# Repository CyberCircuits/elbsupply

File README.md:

## ElbSupply - A simple linear bench supply

ElbSupply is a linear bench power supply with an output voltage range of 0-20V and output current range of 0-3A.

Here are the OSHpark renderings of the boards:

For project details visit the [project page on Hackaday.io](https://hackaday.io/project/4407-elbsupply-simple-linear-bench-supply)

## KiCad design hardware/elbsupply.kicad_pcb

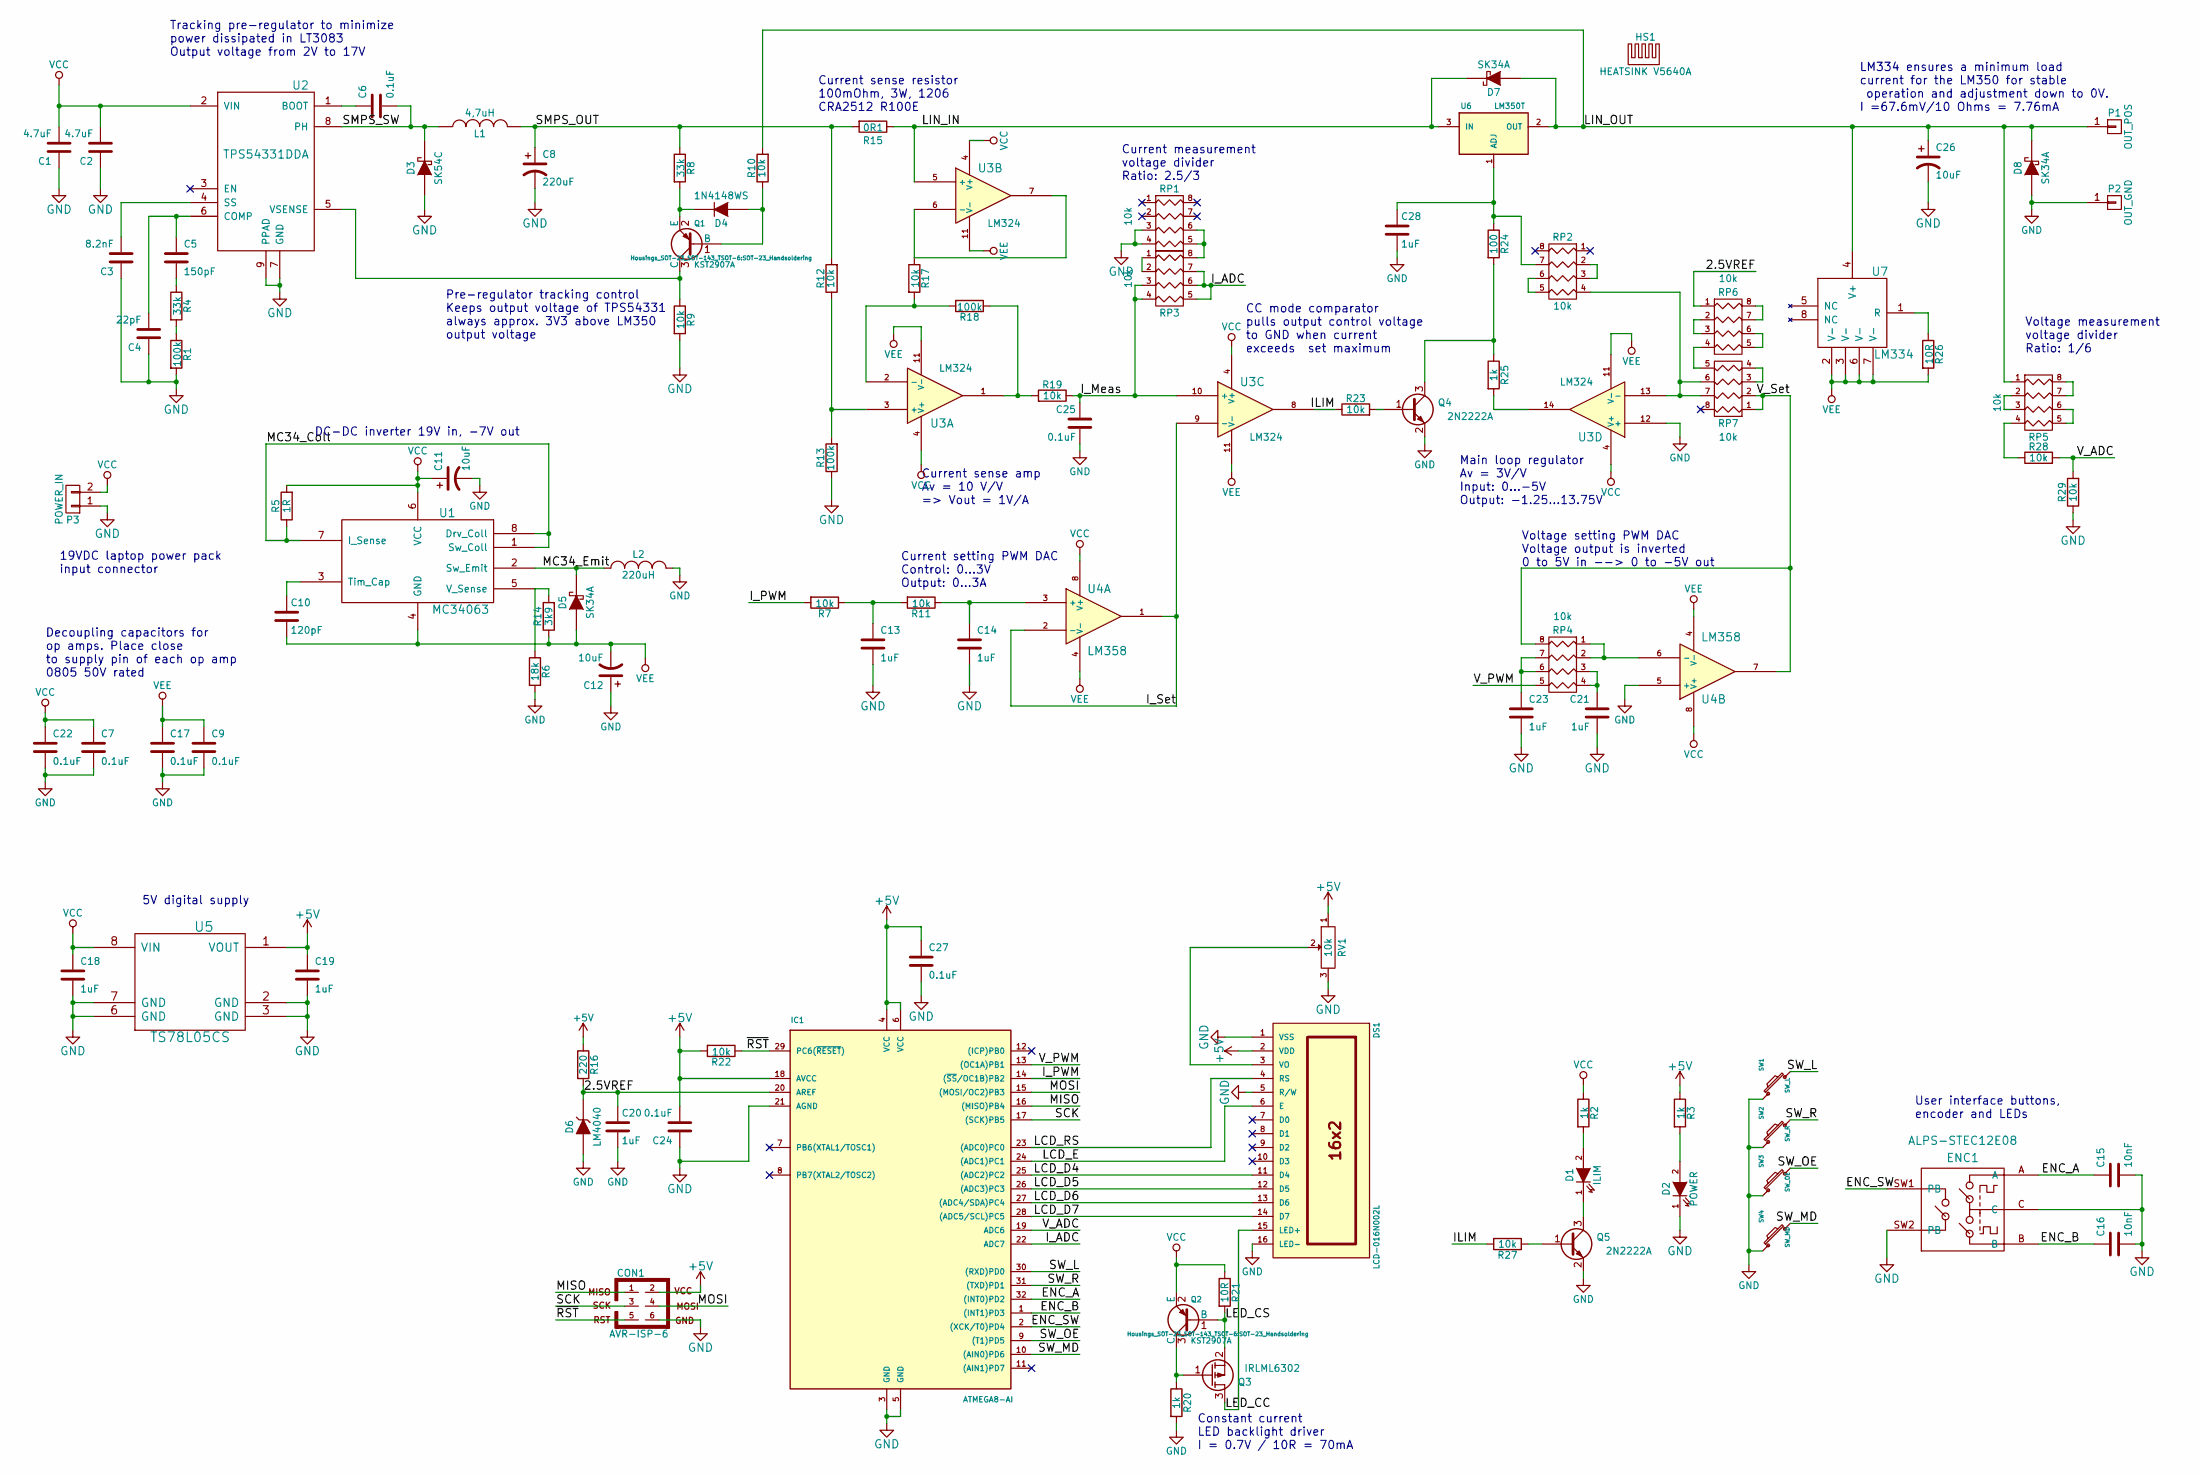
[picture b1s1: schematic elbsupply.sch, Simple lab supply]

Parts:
C1, C2: 4.7uF; C_0805_HandSoldering
C3: 8.2nF; C_0603_HandSoldering
C4: 22pF; C_0603_HandSoldering
C5: 150pF; C_0603_HandSoldering
C6, C7, C9, C17, C22, C24, C25, C27: 0.1uF; C_0805_HandSoldering
C8: 220uF; c_elec_8x10.5
C10: 120pF; C_0603_HandSoldering
C11, C26: 10uF; c_elec_4x4.5
C12: 10uF; C_0805_HandSoldering
C13, C14, C18, C19, C20, C21, C23, C28: 1uF; C_0805_HandSoldering
C15, C16: 10nF; C_0603_HandSoldering
CON1: AVR-ISP-6; Pin_Header_Straight_2x03
D1: ILIM; LED-0805
D2: POWER; LED-0805
D3: SK54C; Diode-SMC_Handsoldering
D4: 1N4148WS; SOD-323
D5, D7, D8: SK34A; DO-214-AC_SMA
D6: LM4040; SOT-23_Handsoldering
DS1: LCD-016N002L; LCD16X2
ENC1: ALPS-STEC12E08
HS1: HEATSINK V5640A; Heatsink-V5640A
IC1: ATMEGA8-AI; TQFP-32_7x7mm_Pitch0.8mm
L1: 4,7uH; 242418FPS-Fastron
L2: 220uH; 242418FPS-Fastron
P1: OUT_POS; SKS-PK10A
P2: OUT_GND; SKS-PK10A
P3: POWER_IN; bornier2
Q1, Q2: KST2907A; SOT-23_Handsoldering
Q3: IRLML6302; SOT-23_Handsoldering
Q4, Q5: 2N2222A; SOT-23_Handsoldering
R1, R13, R18: 100k; R_0603_HandSoldering
R2, R3, R20, R25: 1k; R_0603_HandSoldering
R4, R8: 33k; R_0603_HandSoldering
R5: 1R; R_0805_HandSoldering
R6: 18k; R_0603_HandSoldering
R7, R9, R10, R11, R12, R17, R19, R22, R23, R27, R28, R29: 10k; R_0603_HandSoldering
R14: 3k9; R_0603_HandSoldering
R15: 0R1; CRA2512-Bourns
R16: 220; R_0603_HandSoldering
R21: 10R; R_0603_HandSoldering
R24: 100; R_0603_HandSoldering
R26: 10R; R_0805_HandSoldering
RP1, RP2, RP3, RP4, RP5, RP6, RP7: 10k; YC164-Yageo-Handsoldering
RV1: 10k; BITech-23B
SW1: SW_L; Button-SMT-standard
SW2: SW_R; Button-SMT-standard
SW3: SW_OE; Button-SMT-standard
SW4: SW_MD; Button-SMT-standard
U1: MC34063; SO8
U2: TPS54331DDA; SO8-PowerPAD
U3: LM324; SO14
U4: LM358; SO8
U5: TS78L05CS; SO8
U6: LM350T; TO-220
U7: LM334; SO8

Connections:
+5V: C19.1, C24.2, C27.1, CON1.2, DS1.2 (VDD), IC1.4 (VCC), IC1.6 (VCC), IC1.18 (AVCC), R3.1, R16.1, R22.2, RV1.1, U5.1 (VOUT)
/2.5VREF: C20.1, D6.1 (K), IC1.20 (AREF), R16.2, RP6.1
/ENC_A: C15.1, ENC1.A, IC1.32 ((INT0)PD2)
/ENC_B: C16.1, ENC1.B, IC1.1 ((INT1)PD3)
/ENC_SW: ENC1.SW1 (PB), IC1.2 ((XCK/T0)PD4)
/ILIM: R23.1, R27.2, U3.8
/I_ADC: IC1.22 (ADC7), RP3.5 (R4), RP3.6 (R3), RP3.7 (R2)
/I_Meas: C25.1, R19.1, RP3.3, RP3.4, U3.10 (+)
/I_PWM: IC1.14 ((~SS~/OC1B)PB2), R7.2
/I_Set: U3.9 (-), U4.1, U4.2 (-)
/LCD_D4: DS1.11 (D4), IC1.25 ((ADC2)PC2)
/LCD_D5: DS1.12 (D5), IC1.26 ((ADC3)PC3)
/LCD_D6: DS1.13 (D6), IC1.27 ((ADC4/SDA)PC4)
/LCD_D7: DS1.14 (D7), IC1.28 ((ADC5/SCL)PC5)
/LCD_E: DS1.6 (E), IC1.24 ((ADC1)PC1)
/LCD_RS: DS1.4 (RS), IC1.23 ((ADC0)PC0)
/LED_CC: DS1.15 (LED+), Q3.3 (D)
/LED_CS: Q2.1 (B), Q3.2 (S), R21.2
/LIN_IN: D7.2 (K), R15.1, U3.5 (+), U6.3 (IN)
/LIN_OUT: C26.1, D7.1 (A), D8.2 (K), P1.1, R10.2, RP5.1, U6.2 (OUT), U7.4 (V+)
/MC34_Coll: R5.1, U1.1 (Sw_Coll), U1.7 (I_Sense), U1.8 (Drv_Coll)
/MC34_Emit: D5.2 (K), L2.1, U1.2 (Sw_Emit)
/MISO: CON1.1, IC1.16 ((MISO)PB4)
/MOSI: CON1.4, IC1.15 ((MOSI/OC2)PB3)
/SCK: CON1.3, IC1.17 ((SCK)PB5)
/SMPS_OUT: C8.1, L1.2, R8.1, R12.2, R15.2
/SMPS_SW: C6.2, D3.2 (K), L1.1, U2.8 (PH)
/SW_L: IC1.30 ((RXD)PD0), SW1.2
/SW_MD: IC1.10 ((AIN0)PD6), SW4.2
/SW_OE: IC1.9 ((T1)PD5), SW3.2
/SW_R: IC1.31 ((TXD)PD1), SW2.2
/V_ADC: IC1.19 (ADC6), R28.2, R29.2
/V_PWM: IC1.13 ((OC1A)PB1), RP4.5 (R4)
/V_Set: RP4.8 (R1), RP7.1, RP7.2, U4.7
/~RST~: CON1.5, IC1.29 (PC6(~RESET~)), R22.1
GND: C1.1, C2.1, C3.1, C4.1, C7.2, C8.2, C9.2, C11.2, C12.1, C13.2, C14.2, C15.2, C16.2, C17.2, C18.2, C19.2, C20.2, C21.2, C22.2, C23.2, C24.1, C25.2, C26.2, C27.2, C28.2, CON1.6, D2.1 (K), D3.1 (A), D6.2 (A), D8.1 (A), DS1.1 (VSS), DS1.5 (R/W), DS1.16 (LED-), ENC1.C, ENC1.SW2 (PB), IC1.3 (GND), IC1.5 (GND), IC1.21 (AGND), L2.2, P2.1, P3.1, Q4.2 (E), Q5.2 (E), R1.2, R6.2, R9.2, R13.1, R20.2, R29.1, RP1.3, RP1.4, RV1.3, SW1.1, SW2.1, SW3.1, SW4.1, U2.7 (GND), U2.9 (PPAD), U3.12 (+), U4.5 (+), U5.2 (GND), U5.3 (GND), U5.6 (GND), U5.7 (GND)
unnamed: C3.2, U2.4 (SS)
unnamed: C4.2, C5.1, U2.6 (COMP)
unnamed: C5.2, R4.1
unnamed: C6.1, U2.1 (BOOT)
unnamed: C10.1, U1.3 (Tim_Cap)
unnamed: C13.1, R7.1, R11.2
unnamed: C14.1, R11.1, U4.3 (+)
unnamed: C21.1, RP4.3, RP4.4
unnamed: C23.1, RP4.6 (R3), RP4.7 (R2)
unnamed: C28.1, R24.1, RP2.7 (R2), U6.1 (ADJ)
unnamed: D1.1 (K), Q5.3 (C)
unnamed: D1.2 (A), R2.2
unnamed: D2.2 (A), R3.2
unnamed: D4.1 (A), Q1.1 (B), R10.1
unnamed: D4.2 (K), Q1.2 (E), R8.2
unnamed: DS1.3 (VO), RV1.2
unnamed: Q1.3 (C), R9.1, U2.5 (VSENSE)
unnamed: Q2.3 (C), Q3.1 (G), R20.1
unnamed: Q4.1 (B), R23.2
unnamed: Q4.3 (C), R24.2, R25.1
unnamed: Q5.1 (B), R27.1
unnamed: R1.1, R4.2
unnamed: R12.1, R13.2, U3.3 (+)
unnamed: R6.1, R14.2, U1.5 (V_Sense)
unnamed: R17.1, U3.6 (-), U3.7
unnamed: R17.2, R18.2, U3.2 (-)
unnamed: R18.1, R19.2, U3.1
unnamed: R25.2, U3.14
unnamed: R26.1, U7.1 (R)
unnamed: R28.1, RP5.4
unnamed: RP1.5 (R4), RP1.6 (R3), RP3.8 (R1)
unnamed: RP2.2, RP2.3
unnamed: RP2.4, RP7.6 (R3), RP7.7 (R2), U3.13 (-)
unnamed: RP2.5 (R4), RP2.6 (R3)
unnamed: RP3.1, RP3.2
unnamed: RP4.1, RP4.2, U4.6 (-)
unnamed: RP5.2, RP5.3
unnamed: RP5.5 (R4), RP5.6 (R3)
unnamed: RP5.7 (R2), RP5.8 (R1)
unnamed: RP6.2, RP6.3
unnamed: RP6.4, RP7.5 (R4)
unnamed: RP6.5 (R4), RP6.6 (R3)
unnamed: RP6.7 (R2), RP6.8 (R1)
unnamed: RP7.3, RP7.4
VCC: C1.2, C2.2, C7.1, C11.1, C18.1, C22.1, P3.2, Q2.2 (E), R2.1, R5.2, R21.1, U1.6 (VCC), U2.2 (VIN), U3.4 (V+), U4.8 (V+), U5.8 (VIN)
VEE: C9.1, C10.2, C12.2, C17.1, D5.1 (A), R14.1, R26.2, U1.4 (GND), U3.11 (V-), U4.4 (V-), U7.2 (V-), U7.3 (V-), U7.6 (V-), U7.7 (V-)

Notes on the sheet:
Current sense amp Av = 10 V/V => Vout = 1V/A
Main loop regulator Av = 3V/V Input: 0...-5V Output: -1.25...13.75V
Current setting PWM DAC Control: 0...3V Output: 0...3A
Voltage setting PWM DAC Voltage output is inverted 0 to 5V in --> 0 to -5V out
Pre-regulator tracking control Keeps output voltage of TPS54331 always approx. 3V3 above LM350 output voltage
Tracking pre-regulator to minimize power dissipated in LT3083 Output voltage from 2V to 17V
CC mode comparator pulls output control voltage to GND when current exceeds set maximum
Current measurement voltage divider Ratio: 2.5/3
5V digital supply
Current sense resistor 100mOhm, 3W, 1206 CRA2512 R100E
Constant current LED backlight driver I = 0.7V / 10R = 70mA
Decoupling capacitors for op amps. Place close to supply pin of each op amp 0805 50V rated
19VDC laptop power pack input connector
DC-DC inverter 19V in, -7V out
User interface buttons, encoder and LEDs
LM334 ensures a minimum load current for the LM350 for stable operation and adjustment down to 0V. I =67.6mV/10 Ohms = 7.76mA
Voltage measurement voltage divider Ratio: 1/6

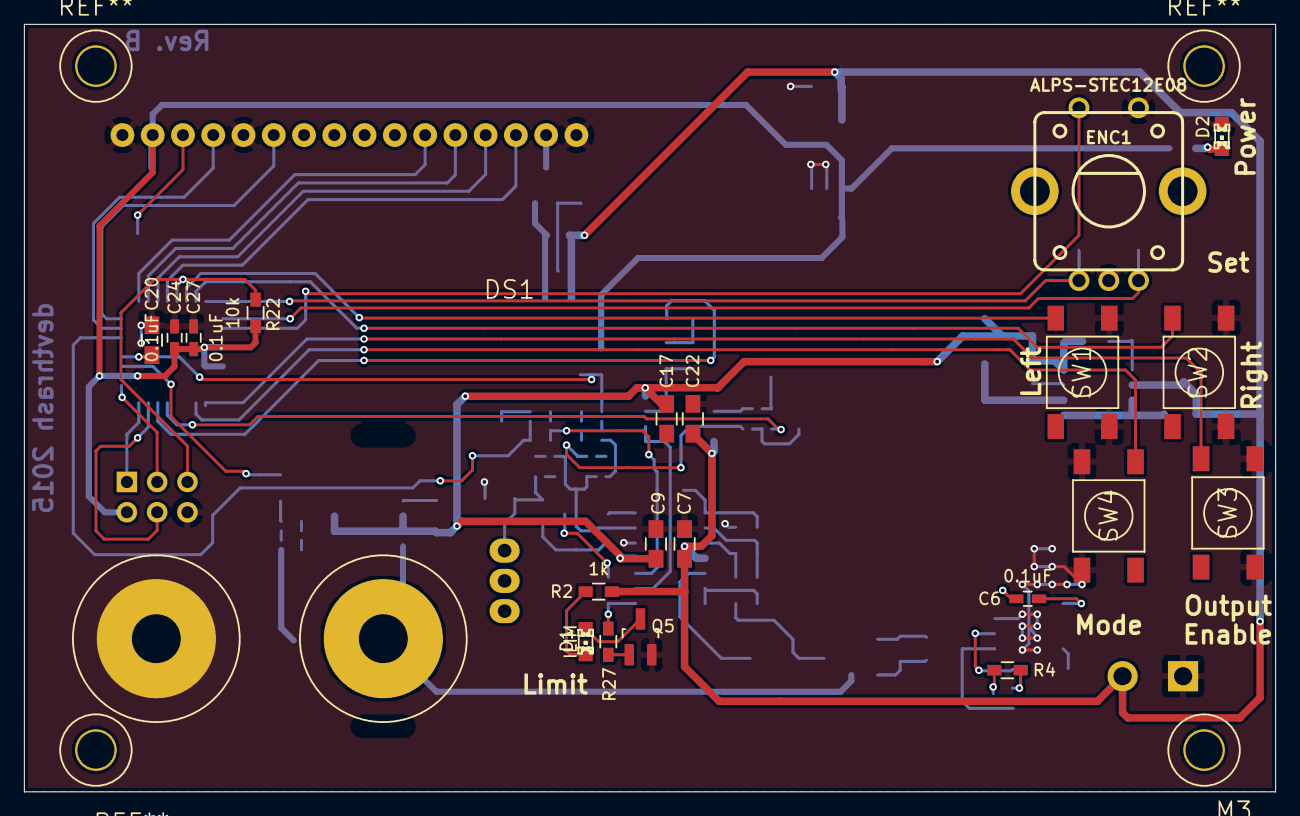
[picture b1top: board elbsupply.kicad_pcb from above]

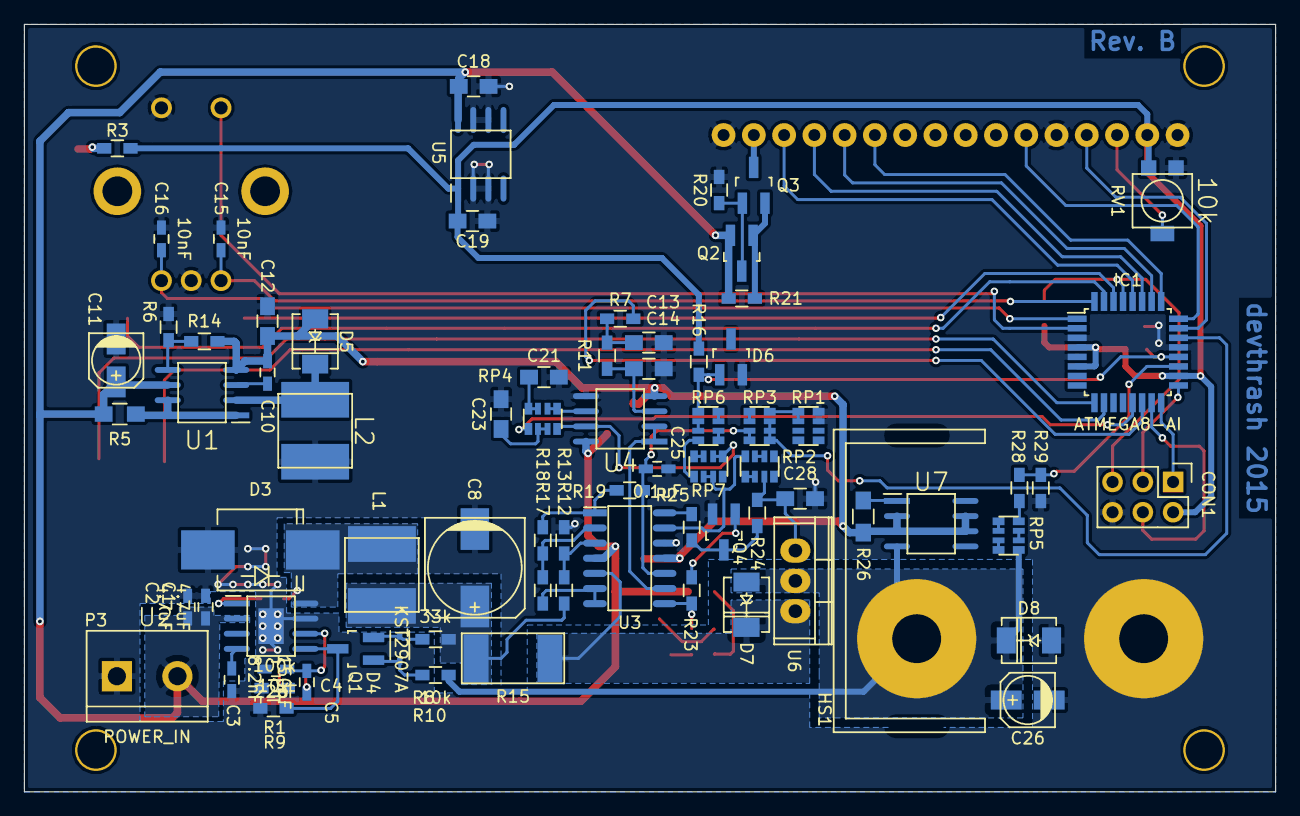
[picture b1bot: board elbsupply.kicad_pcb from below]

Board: 2 copper layers, 105.0 x 64.4 mm, 100 parts (76 on the bottom side), 82 nets.

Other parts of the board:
M3: Screw_PAN_Head_M3

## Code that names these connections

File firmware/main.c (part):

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/* I/O mapping on the PCB
 * 
 * Inputs:
 * Button Left: 			PD0
 * Button right: 			PD1
 * Encoder button: 			PD2
 * Encoder A:				PD3
 * Encoder B:				PD4				
 * Button output enable: 	PD5
 * Button mode: 			PD6
 * 
 * output voltage:			ADC6
 * output current:			ADC7
 * 
 * Outputs:
 * Voltage set PWM:			PB1
 * Current set PWM:			PB2
 * LCD_RS:					PC0
 * LCD_E:					PC1
 * LCD_D4:					PC2
 * LCD_D5:					PC3
 * LCD_D6:					PC4
 * LCD_D7:					PC5
 */
#define BTN_LEFT	0x01
#define BTN_RIGHT	0x02
#define ENC_BTN		0x04
#define ENC_A		0x08
#define ENC_B		0x10
#define BTN_OE 		0x20
#define BTN_MODE	0x40

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
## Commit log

2015-02-24 added pointer to Hackaday.io
2015-02-24 changed pre-regulator to TPS54331DDA, need to calculate exact values
2015-02-24 file clean up
2015-02-27 final Rev. A schematic
2015-03-01 changed 5V regulator for surface mount version
2015-03-01 final Rev. A schematic annotated
2015-03-01 partially done with footprint association
2015-03-03 slight schematic changes, footprint association almost done
2015-03-04 component footprint association done
2015-03-04 added screw terminal power input
2015-03-04 started PCB layout, fixed some footprint association
2015-03-04 binding post distance is now 3/4 inch
2015-03-05 fixed Q1 footprint issues
2015-03-05 continued layout
2015-03-07 parts placement largely finished
2015-03-07 added PCB mounting holes, need repositioning of connectors and LCD
2015-03-08 LT3083 output capacitors exchanged for electrolytics
2015-03-08 rev. A routing finished
2015-03-08 added two more switches for cleaner UI
2015-03-08 final reviision A routing done, need to add some logo
2015-03-08 rev A board, ordered
2015-03-08 quickly added LM334 constant current sink to ensure stable operation of LT3083
2015-03-09 made a mistake in LCD pinout, fixed in schematic, needs to be fixed on revision B board
2015-03-09 started firmware development
2015-03-10 added ADC routines
2015-03-11 added PWM initialization
2015-03-12 PWM low level init and voltage to pulsewidth conversion code added
2015-03-13 fixed wrong LCD connection in Schematic
2015-03-13 added prerequisites for FSM implementation
2015-03-13 split PWM functions into separate files
2015-03-14 decided on LCD layout for UI
2015-03-14 finished LCD update code
2015-03-15 added cursor setting code
2015-03-15 FSM output enable mode added
2015-03-15 added output mode defines for easier readability
2015-03-15 added encoder voltage and current setting
2015-03-15 broke up FSM into function for each state with return value as next state of FSM
2015-03-15 fixed some style
2015-03-16 added switch debouncing
2015-03-16 added production outputs and BOM files to .gitignore
2015-03-16 removed duplicate entries
2015-03-16 improved debouncing further, now returns only 1 if switch status has changed
2015-03-16 finished initial implementation of FSM idle state
2015-03-16 make sure that FSM idle state is actually executed
2015-03-16 fixed issues in Idle state, removed unnecessary stateCurret FSM register
2015-03-19 fixed button read
2015-03-22 fixed readme
2015-03-22 ignoring gerber files
2015-03-22 added board renderings
2015-04-11 fixed LCD library so data and control lines can be on same physical port
2015-04-11 display buffer is split into individual lines for easier formatting
2015-04-11 mostly fixed LCD display routines and updating
2015-04-13 improved user interface
2015-04-13 changed components to improve loop stability
2015-04-18 improved current limiting circuit, constant current LCD LED backlight driver
2015-04-18 changed voltage measurement divider to new voltage range
2015-04-18 changed max output voltage
2015-04-19 exchanged LT3083 for LM350, added negative rail and offset amplifiers
2015-04-19 extended negative rail to -7V, improved voltage adjustment
2015-04-21 adjusted minimum load current, added heatsink
2015-04-21 code cleanup, added comments to explain encoder decoding
2015-04-23 main control voltage op amp has voltage shifted down by 1.25V for LM350 0V output
2015-04-23 changed tracking preregulator output tracking and compensation
2015-04-23 finalized Rev. B schematic, started new component association
2015-04-24 Rev B component association done
2015-04-25 started new layout
2015-04-27 continued board layout
2015-05-02 RevB layout finished
2015-05-02 rev B. ordered, exchnaged heatsink slots for PCB cutouts
2015-05-07 added Rev. B board renderings
2015-05-30 enabled pull-up resistors on needed pins
2015-05-30 corrected button association for Rev. B PCB
2015-05-30 corrected voltage measurement and voltage set routines for Rev. B board
2015-05-30 fixed voltage set buffer amp gain
2015-05-30 fixed current mode pull down transistor, current limiting works as expected
